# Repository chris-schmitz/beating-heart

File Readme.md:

# Beating Heart Pendant

The beating heart pendant is a small attiny85 driven pendant that I'm using to learn Eagle CAD, the Bantam Othermill, and general circuit board design.

I'm still working on the design and assembly portion of the project. As I 3D model the case and cover I'll add the models and dxfs necessary to build the entire pendant.

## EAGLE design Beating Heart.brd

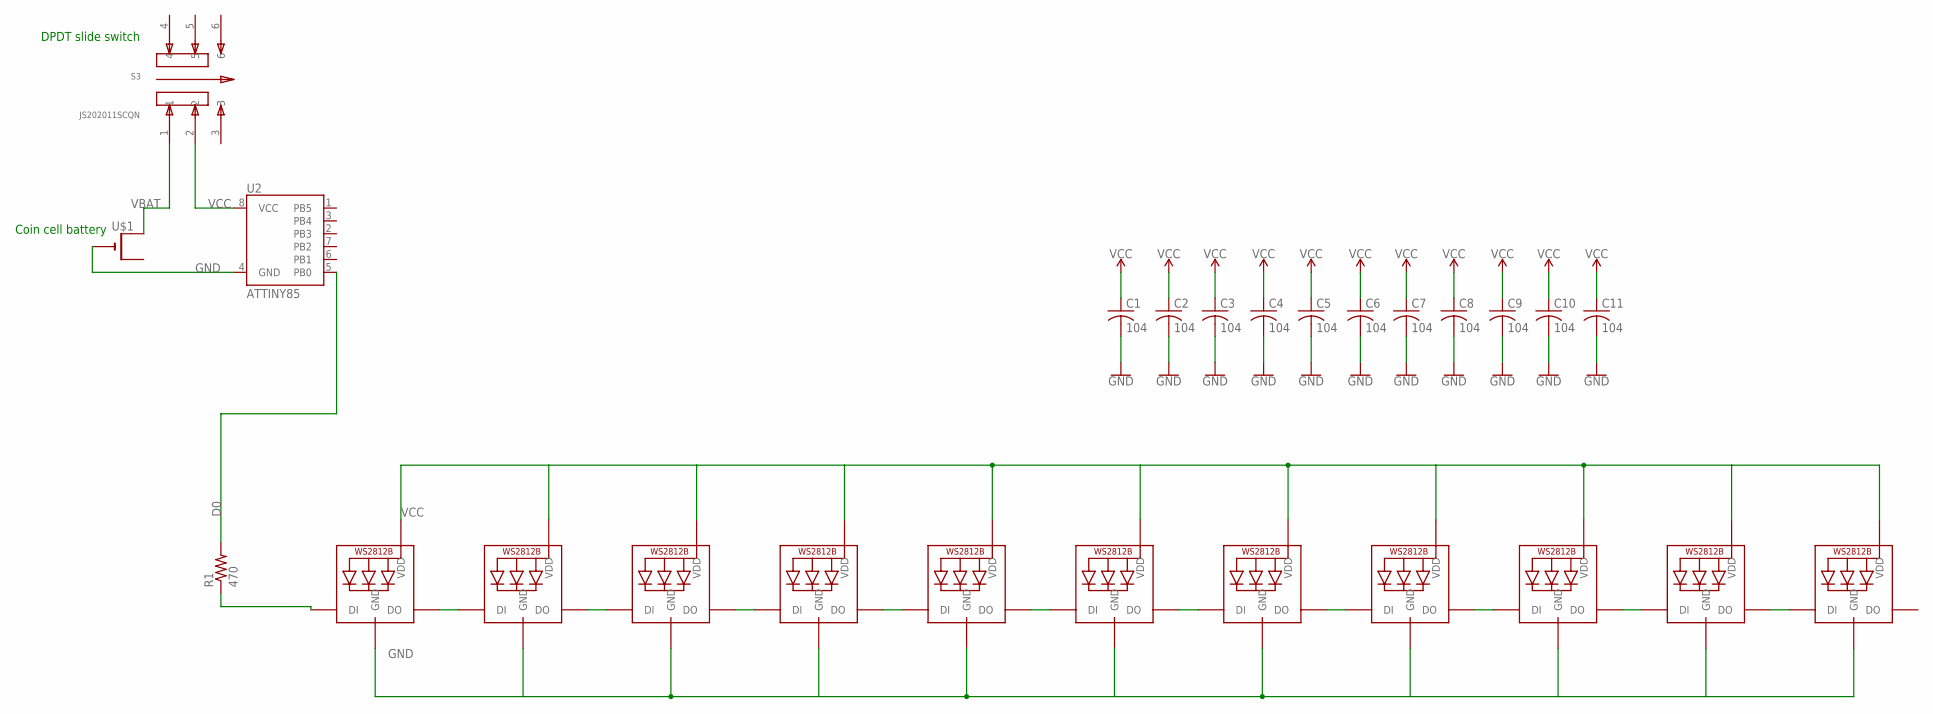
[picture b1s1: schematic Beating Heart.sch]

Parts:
C1, C2, C3, C4, C5, C6, C7, C8, C9, C10, C11: 104; C0805K
LED1, LED2, LED3, LED4, LED5, LED6, LED7, LED8, LED9, LED10, LED11: WS2812B5050; WS2812B
R1: 470; M0805
S3: JS202011SCQN; SW_JS202011SCQN
U2: ATTINY85
U$1: CR1220SMT; CR1220-SMD

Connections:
D0: R1.2, U2.5 (PB0)
GND: C1.2, C2.2, C3.2, C4.2, C5.2, C6.2, C7.2, C8.2, C9.2, C10.2, C11.2, LED1.3-GND (GND), LED2.3-GND (GND), LED3.3-GND (GND), LED4.3-GND (GND), LED5.3-GND (GND), LED6.3-GND (GND), LED7.3-GND (GND), LED8.3-GND (GND), LED9.3-GND (GND), LED10.3-GND (GND), LED11.3-GND (GND), U2.4 (GND), U$1.-
unnamed: LED1.2-DOUT (DO), LED2.4-DIN (DI)
unnamed: LED2.2-DOUT (DO), LED3.4-DIN (DI)
unnamed: LED3.2-DOUT (DO), LED4.4-DIN (DI)
unnamed: LED4.2-DOUT (DO), LED5.4-DIN (DI)
unnamed: LED5.2-DOUT (DO), LED6.4-DIN (DI)
unnamed: LED6.2-DOUT (DO), LED7.4-DIN (DI)
unnamed: LED7.2-DOUT (DO), LED8.4-DIN (DI)
unnamed: LED8.2-DOUT (DO), LED9.4-DIN (DI)
unnamed: LED9.2-DOUT (DO), LED10.4-DIN (DI)
unnamed: LED10.2-DOUT (DO), LED11.4-DIN (DI)
unnamed: LED1.4-DIN (DI), R1.1
VBAT: S3.1, U$1.+$1 (+)
VCC: C1.1, C2.1, C3.1, C4.1, C5.1, C6.1, C7.1, C8.1, C9.1, C10.1, C11.1, LED1.1-VDD (VDD), LED2.1-VDD (VDD), LED3.1-VDD (VDD), LED4.1-VDD (VDD), LED5.1-VDD (VDD), LED6.1-VDD (VDD), LED7.1-VDD (VDD), LED8.1-VDD (VDD), LED9.1-VDD (VDD), LED10.1-VDD (VDD), LED11.1-VDD (VDD), S3.2, U2.8 (VCC)

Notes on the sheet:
Coin cell battery
DPDT slide switch

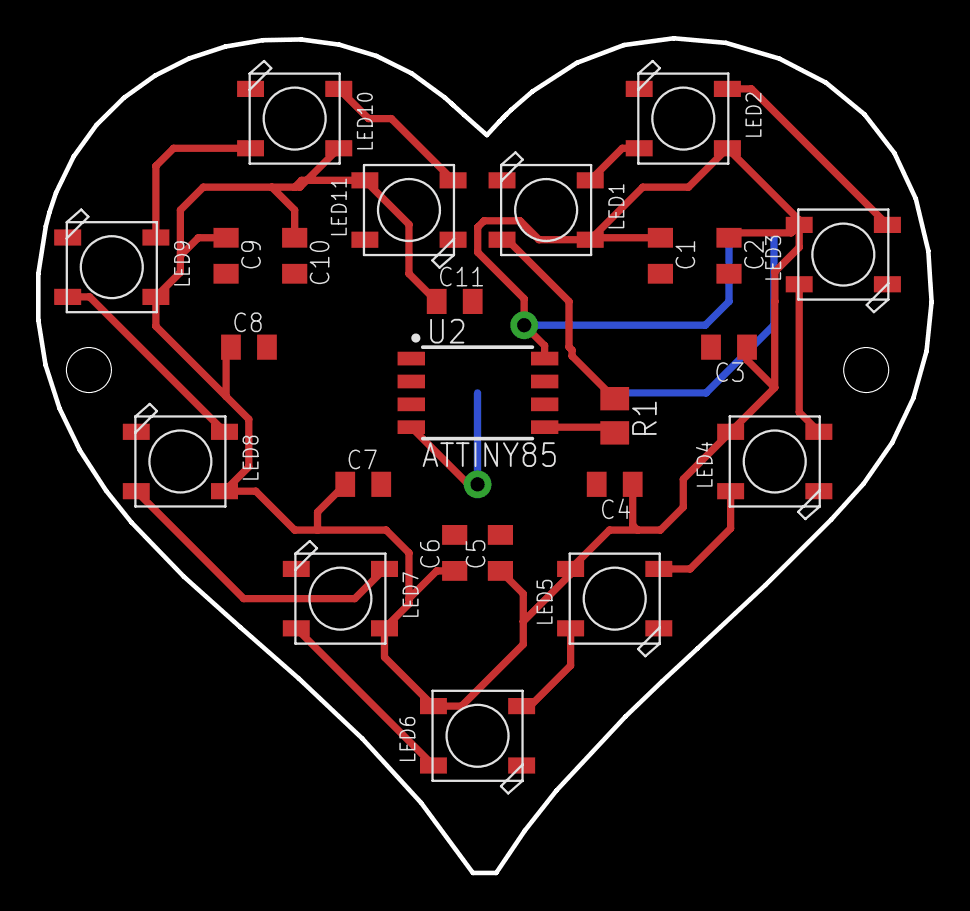
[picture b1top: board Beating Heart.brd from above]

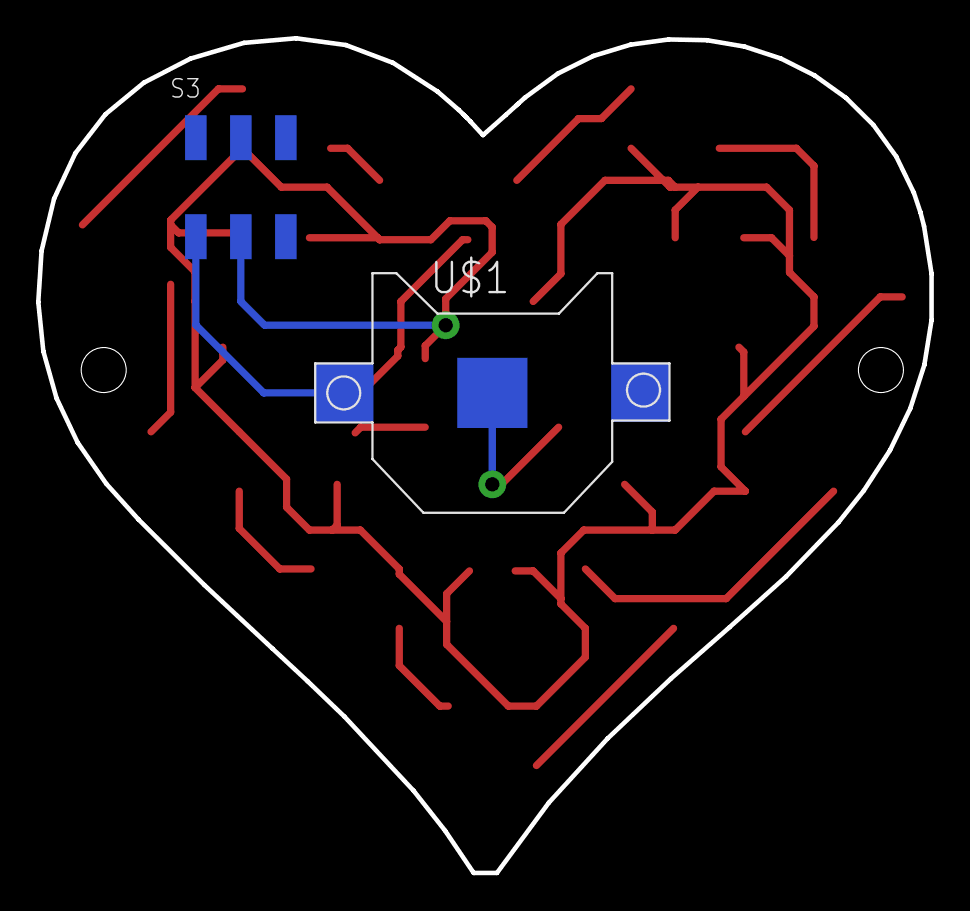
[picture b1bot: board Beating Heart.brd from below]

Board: 2 copper layers, 49.6 x 46.4 mm, 26 parts (2 on the bottom side), 15 nets.

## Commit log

2020-01-14 Adds art for the heart
2020-01-15 adds plans for board
2020-01-18 Adds bantam mill layout
2020-01-18 adds updates to board and schematic
2020-01-18 Moves circuit board design into a subfolder. Adds a readme
2020-01-18 adds detail to readme and ino file for the code
2020-01-31 Adds changes that I made a while ago and I don't remember what's different :|

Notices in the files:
parts and their libraries:
SparkFun-IC-Microcontroller: Licensing: Creative Commons ShareAlike 4.0 International - https://creativecommons.org/licenses/by-sa/4.0
